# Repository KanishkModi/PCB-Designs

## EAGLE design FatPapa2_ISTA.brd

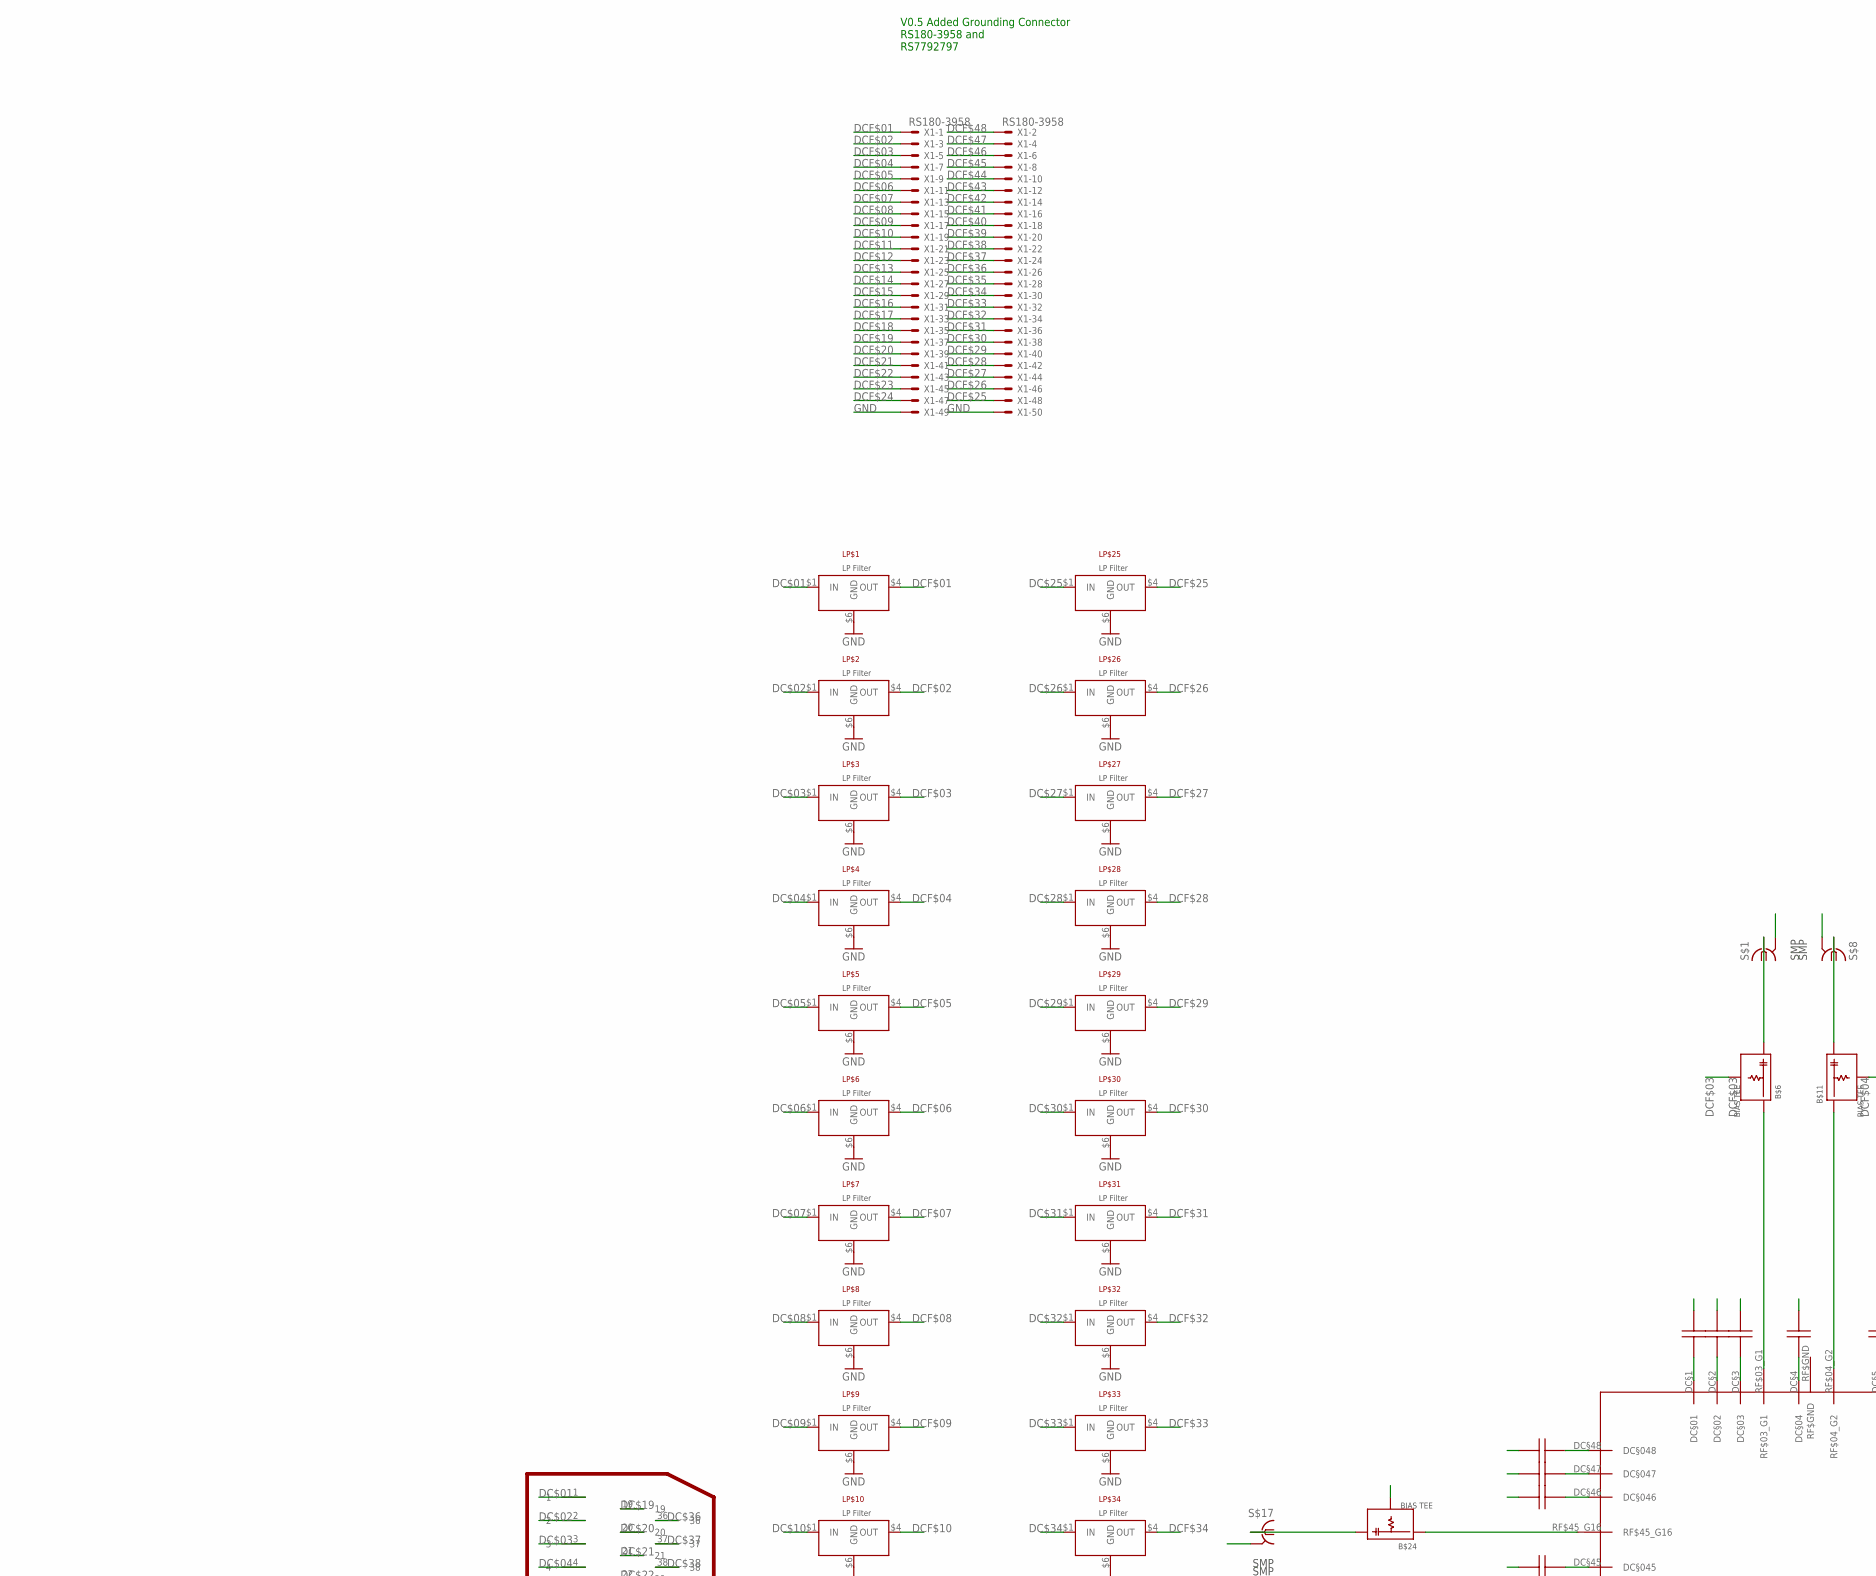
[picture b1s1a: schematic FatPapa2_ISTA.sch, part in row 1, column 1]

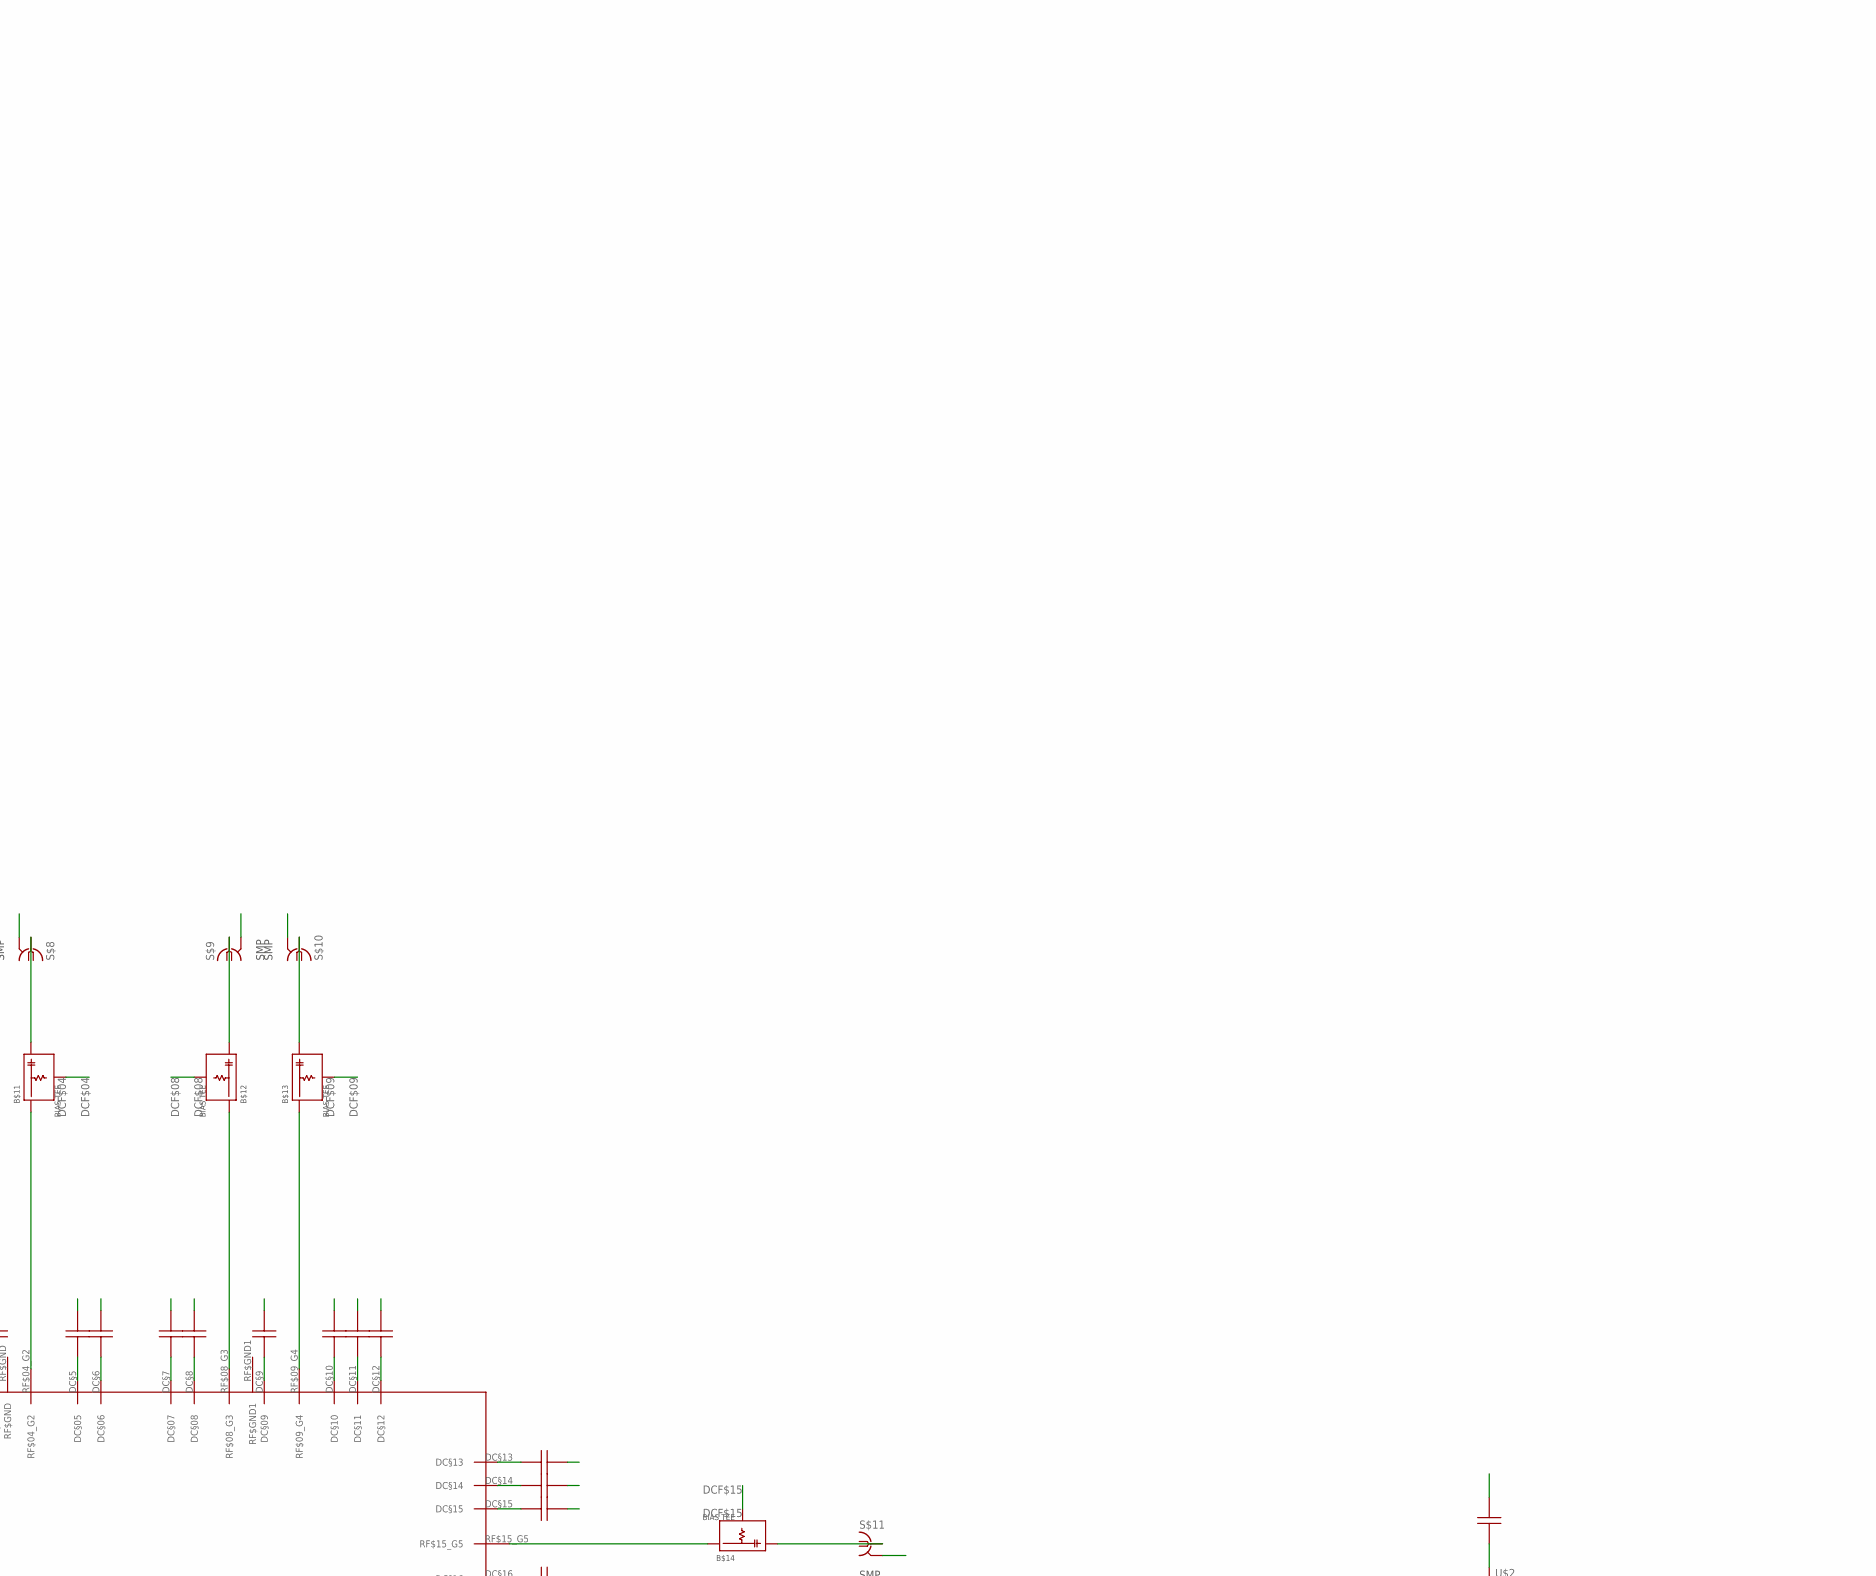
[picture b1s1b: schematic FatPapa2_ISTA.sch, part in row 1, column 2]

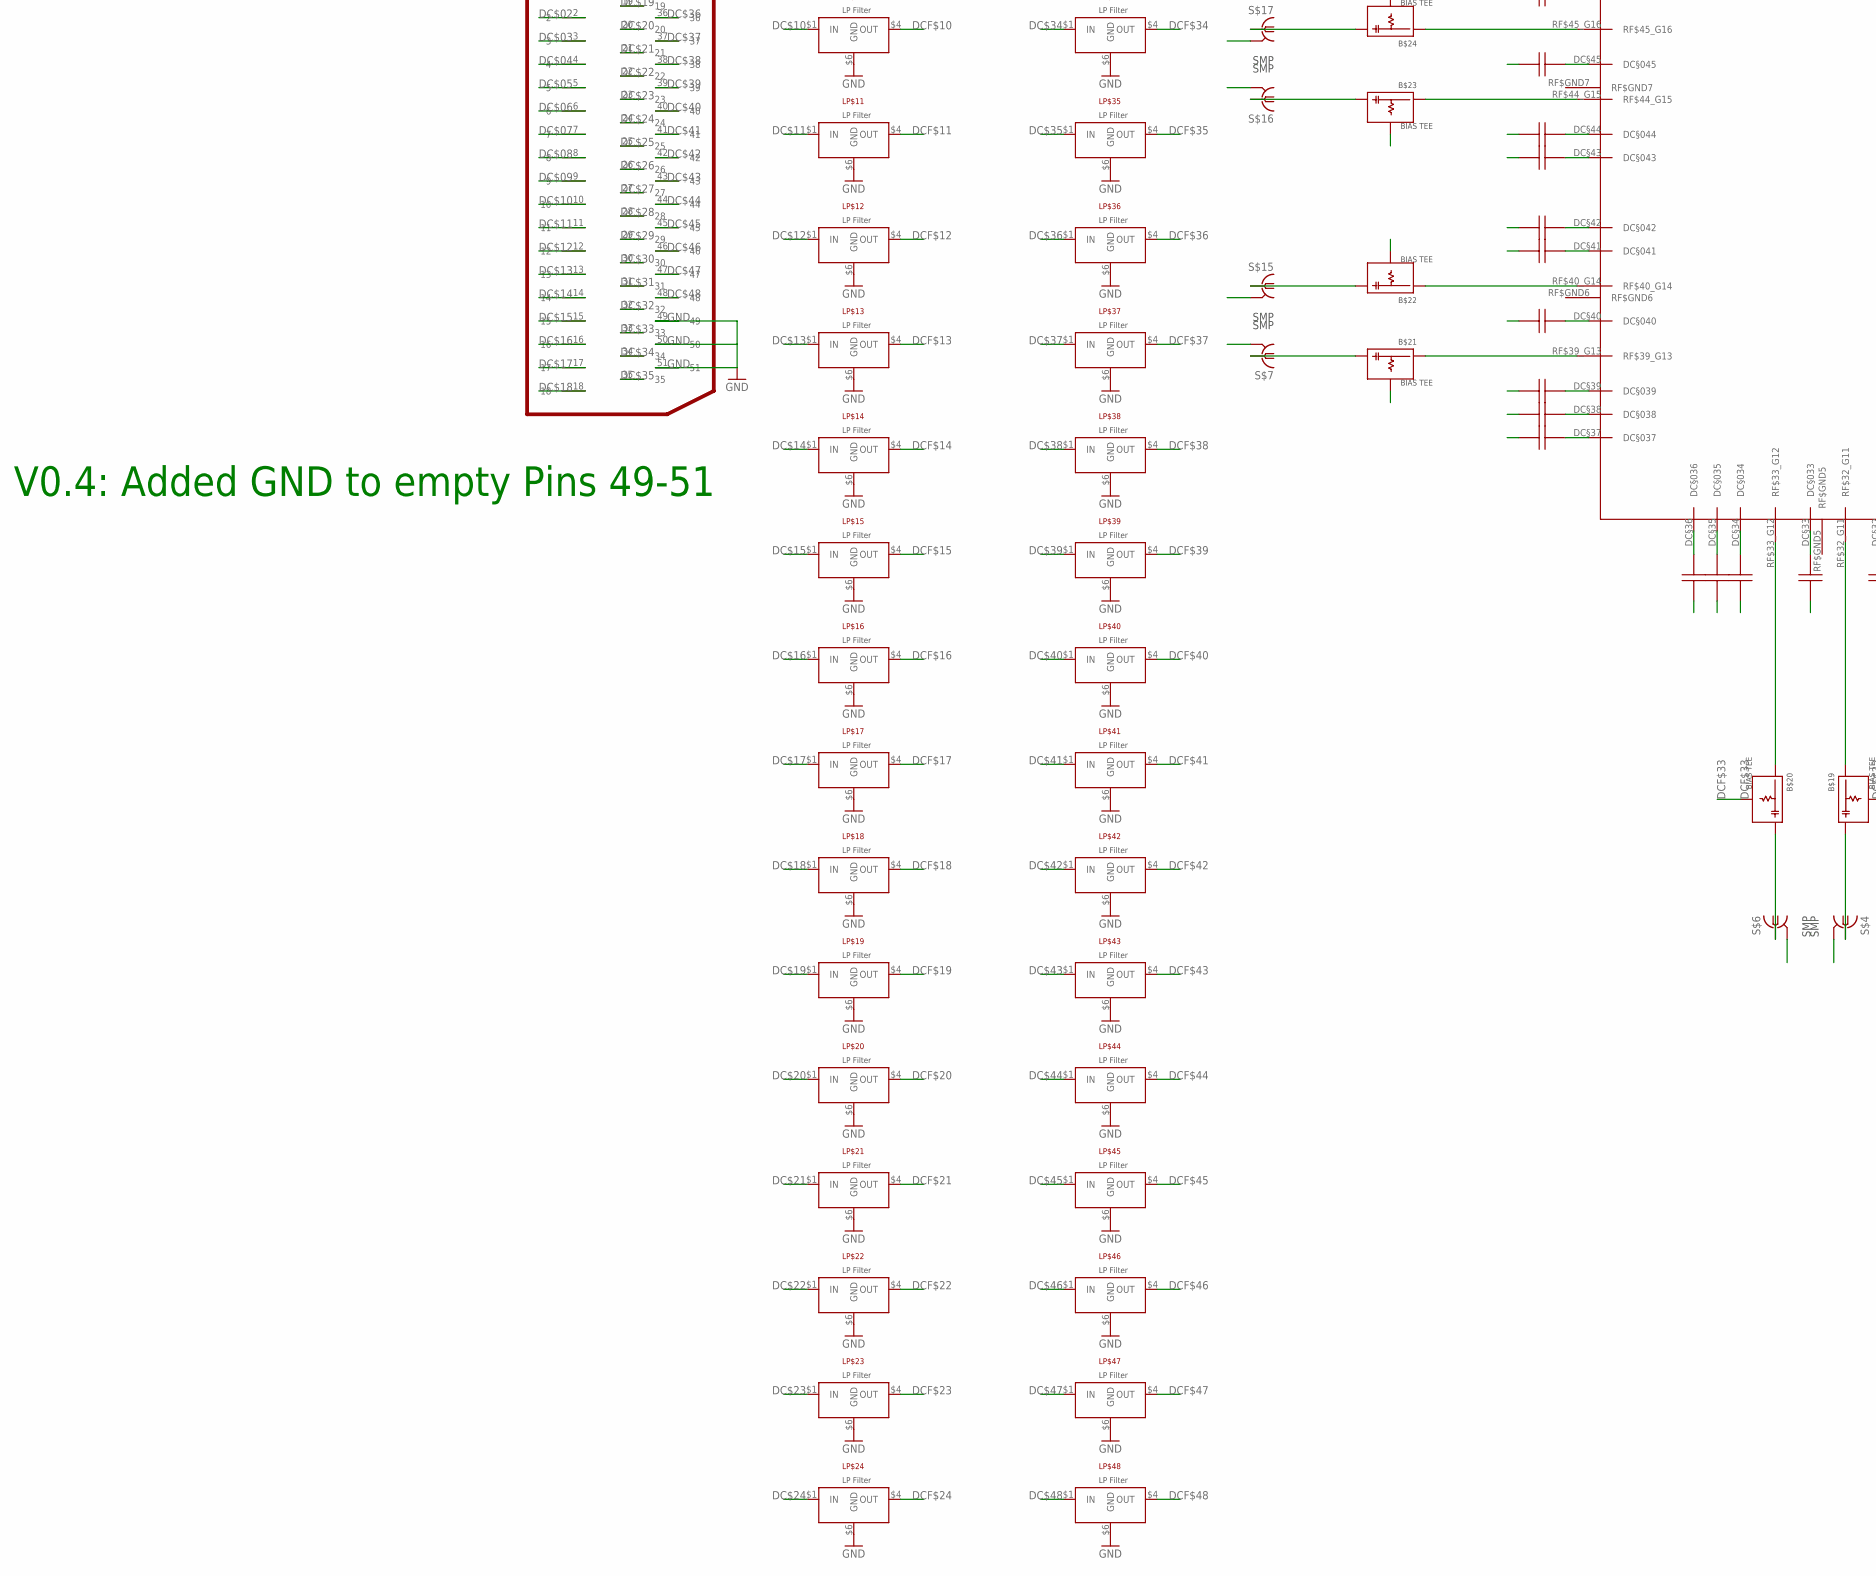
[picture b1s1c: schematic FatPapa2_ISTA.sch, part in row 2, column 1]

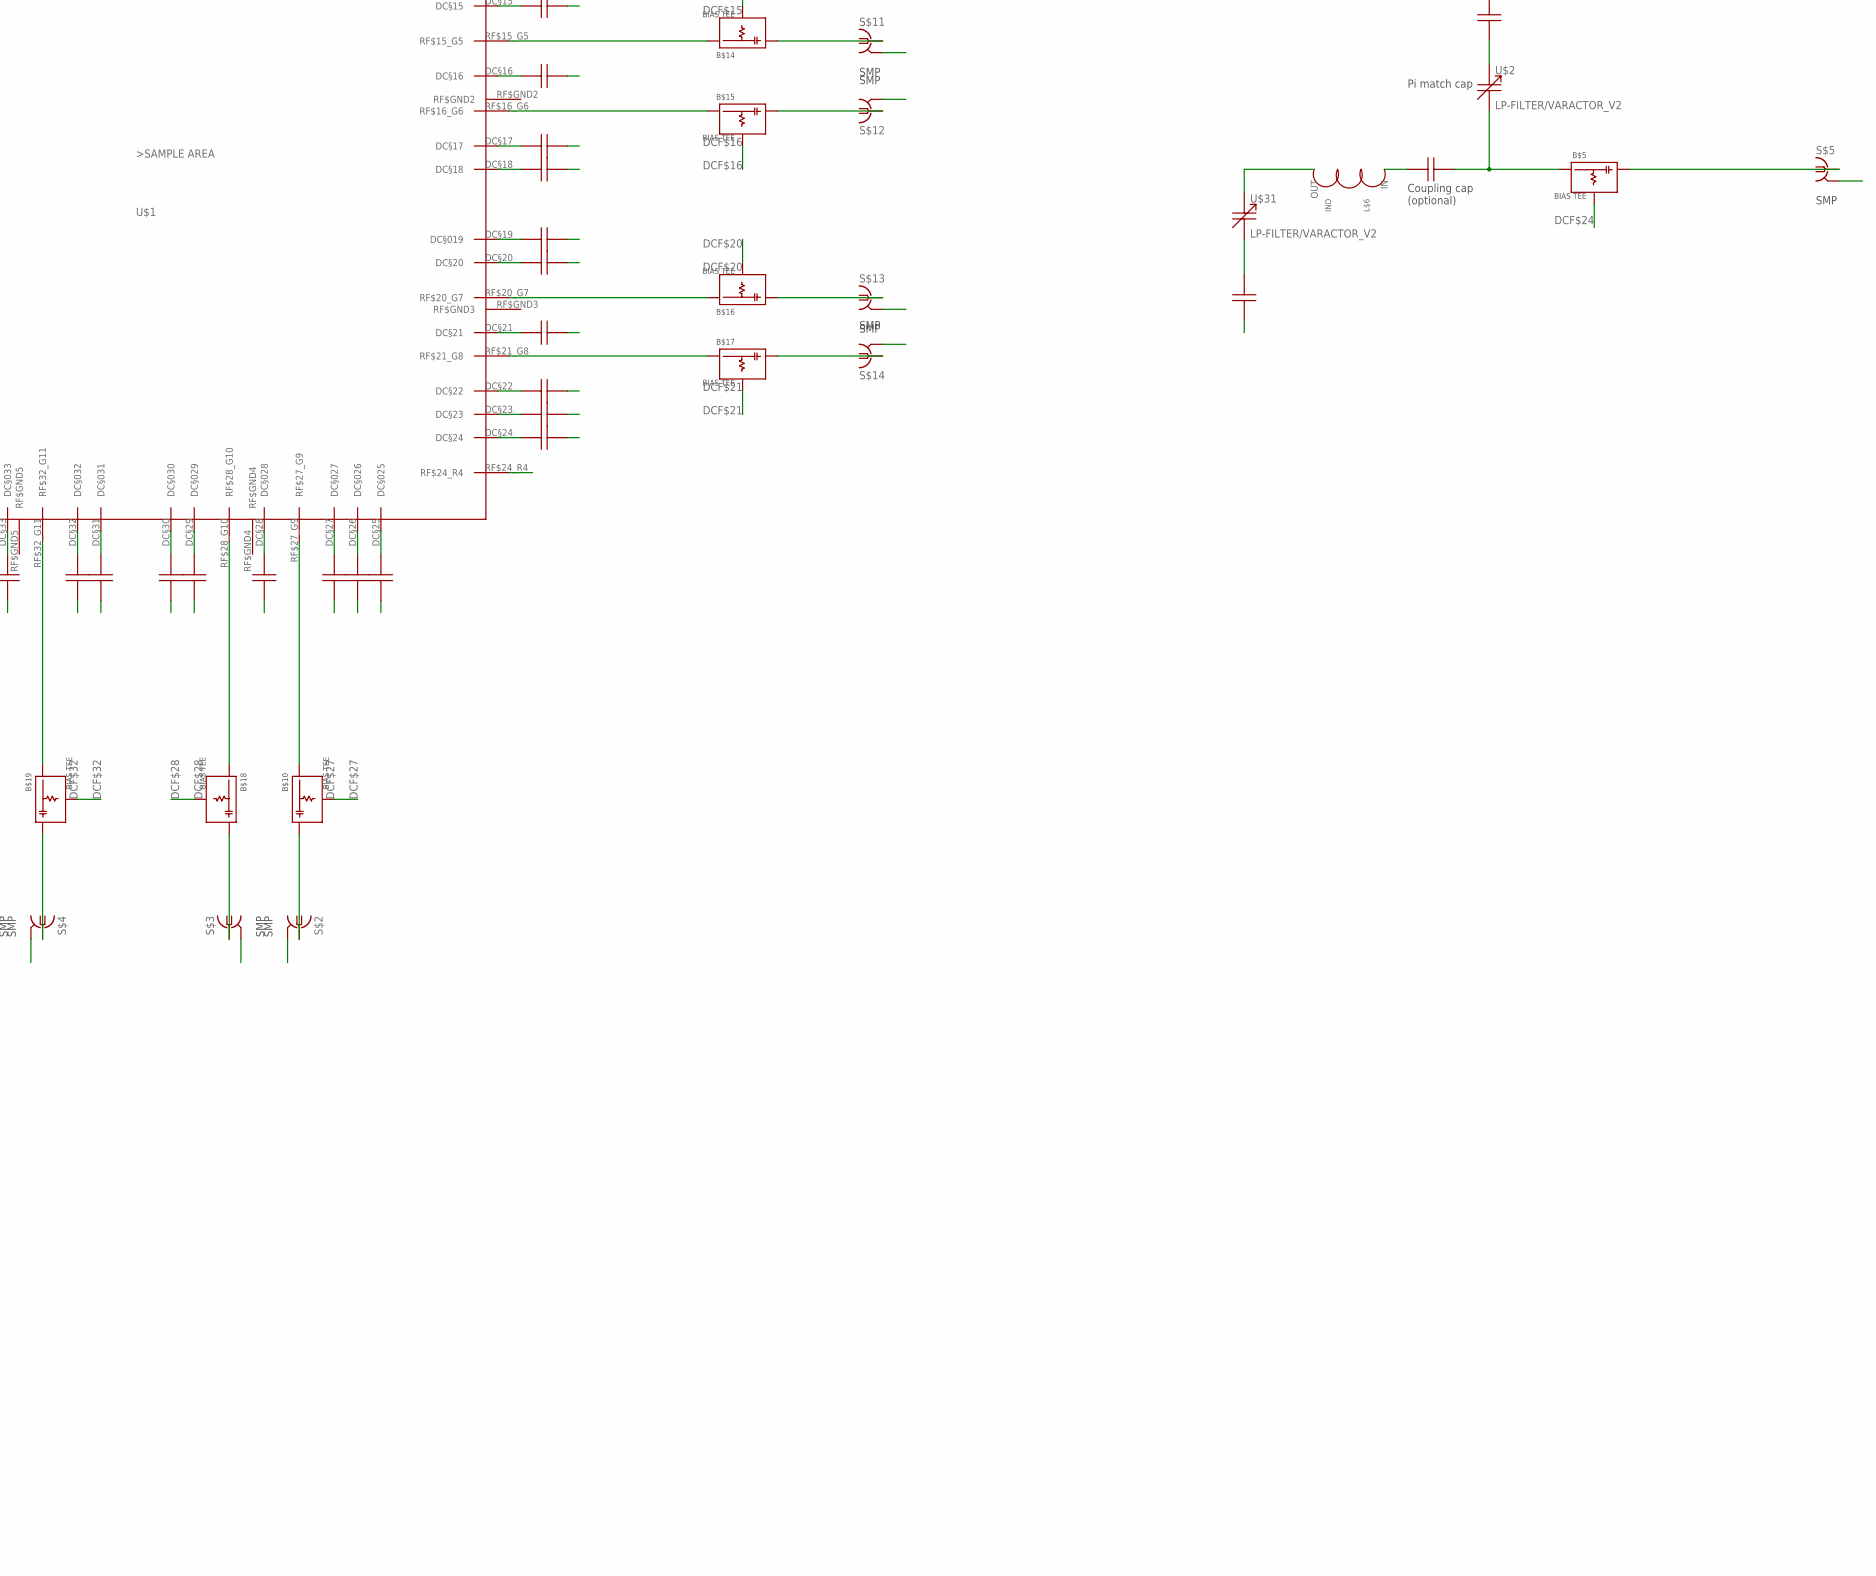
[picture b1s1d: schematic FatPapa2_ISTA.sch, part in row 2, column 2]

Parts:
B$5: BIASTEETHINUP; BIAS_TEE_UP_0603_THIN
B$6, B$10, B$11, B$14, B$15, B$18, B$21, B$22: BIASTEEDOWN1; BIAS_TEE_DOWN_0603
B$12, B$13, B$16, B$17, B$19, B$20, B$23, B$24: BIASTEEUP1; BIAS_TEE_UP_0603
L$6: L_MATCH
LP$1, LP$2, LP$3, LP$4, LP$5, LP$6, LP$7, LP$8, LP$9, LP$10, LP$11, LP$12, LP$13, LP$14, LP$15, LP$16, LP$17, LP$18, LP$19, LP$20, LP$21, LP$22, LP$23, LP$24, LP$25, LP$26, LP$27, LP$28, LP$29, LP$30, LP$31, LP$32, LP$33, LP$34, LP$35, LP$36, LP$37, LP$38, LP$39, LP$40, LP$41, LP$42, LP$43, LP$44, LP$45, LP$46, LP$47, LP$48: LP-FILTER/1-STAGETOP; LP-FILTER/1_STAGE/OS/0603_TOP
S$1, S$2, S$3, S$4, S$6, S$7, S$8, S$9, S$10, S$11, S$12, S$13, S$14, S$15, S$16, S$17: MC-921WIDE; SMP_STRAIGHT_MINI_WIDE
S$5: MC-921; SMP_STRAIGHT_MINI_WIDE_V1_01_ROUND
U$1: 48DC+24RF_V4.0
U$2, U$31: LP-FILTER/VARACTOR_V2
U$3, U$32: LP-FILTER/CAPACITOR/0603NORMAL; LP-FILTER/CAPACITOR/0603_BOTTOM_V2
U$25: 51_PIN_M83513/11-G
U$33, U$42, U$43, U$44, U$45, U$46, U$47, U$48, U$49, U$50, U$51, U$52, U$53, U$54, U$55, U$56, U$57, U$58, U$59, U$60, U$61, U$62, U$63, U$64, U$65, U$66, U$67, U$68, U$69, U$70, U$71, U$72, U$73, U$74, U$75, U$76, U$77, U$78, U$79, U$80, U$81, U$82, U$83, U$84, U$85, U$86, U$87, U$88, U$89: LP-FILTER/CAPACITOR/0603THIN; LP-FILTER/CAPACITOR/0603_BOTTOM
X1: RS180-3958; SMDSMALL87758-5016

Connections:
DC$01: LP$1.$1 (IN), U$25.1
DC$02: LP$2.$1 (IN), U$25.2
DC$03: LP$3.$1 (IN), U$25.3
DC$04: LP$4.$1 (IN), U$25.4
DC$05: LP$5.$1 (IN), U$25.5
DC$06: LP$6.$1 (IN), U$25.6
DC$07: LP$7.$1 (IN), U$25.7
DC$08: LP$8.$1 (IN), U$25.8
DC$09: LP$9.$1 (IN), U$25.9
DC$10: LP$10.$1 (IN), U$25.10
DC$11: LP$11.$1 (IN), U$25.11
DC$12: LP$12.$1 (IN), U$25.12
DC$13: LP$13.$1 (IN), U$25.13
DC$14: LP$14.$1 (IN), U$25.14
DC$15: LP$15.$1 (IN), U$25.15
DC$16: LP$16.$1 (IN), U$25.16
DC$17: LP$17.$1 (IN), U$25.17
DC$18: LP$18.$1 (IN), U$25.18
DC$19: LP$19.$1 (IN), U$25.19
DC$20: LP$20.$1 (IN), U$25.20
DC$21: LP$21.$1 (IN), U$25.21
DC$22: LP$22.$1 (IN), U$25.22
DC$23: LP$23.$1 (IN), U$25.23
DC$24: LP$24.$1 (IN), U$25.24
DC$25: LP$25.$1 (IN), U$25.25
DC$26: LP$26.$1 (IN), U$25.26
DC$27: LP$27.$1 (IN), U$25.27
DC$28: LP$28.$1 (IN), U$25.28
DC$29: LP$29.$1 (IN), U$25.29
DC$30: LP$30.$1 (IN), U$25.30
DC$31: LP$31.$1 (IN), U$25.31
DC$32: LP$32.$1 (IN), U$25.32
DC$33: LP$33.$1 (IN), U$25.33
DC$34: LP$34.$1 (IN), U$25.34
DC$35: LP$35.$1 (IN), U$25.35
DC$36: LP$36.$1 (IN), U$25.36
DC$37: LP$37.$1 (IN), U$25.37
DC$38: LP$38.$1 (IN), U$25.38
DC$39: LP$39.$1 (IN), U$25.39
DC$40: LP$40.$1 (IN), U$25.40
DC$41: LP$41.$1 (IN), U$25.41
DC$42: LP$42.$1 (IN), U$25.42
DC$43: LP$43.$1 (IN), U$25.43
DC$44: LP$44.$1 (IN), U$25.44
DC$45: LP$45.$1 (IN), U$25.45
DC$46: LP$46.$1 (IN), U$25.46
DC$47: LP$47.$1 (IN), U$25.47
DC$48: LP$48.$1 (IN), U$25.48
DCF$01: LP$1.$4 (OUT), U$1.DC§1 (DC§01), U$42.OUT (2), X1.P$1
DCF$02: LP$2.$4 (OUT), U$1.DC§2 (DC§02), U$43.OUT (2), X1.P$3
DCF$03: B$6.LF, LP$3.$4 (OUT), U$1.DC§3 (DC§03), U$44.OUT (2), X1.P$5
DCF$04: B$11.LF, LP$4.$4 (OUT), U$1.DC§4 (DC§04), U$45.OUT (2), X1.P$7
DCF$05: LP$5.$4 (OUT), U$1.DC§5 (DC§05), U$46.OUT (2), X1.P$9
DCF$06: LP$6.$4 (OUT), U$1.DC§6 (DC§06), U$47.OUT (2), X1.P$11
DCF$07: LP$7.$4 (OUT), U$1.DC§7 (DC§07), U$48.OUT (2), X1.P$13
DCF$08: B$12.LF, LP$8.$4 (OUT), U$1.DC§8 (DC§08), U$49.OUT (2), X1.P$15
DCF$09: B$13.LF, LP$9.$4 (OUT), U$1.DC§9 (DC§09), U$50.OUT (2), X1.P$17
DCF$10: LP$10.$4 (OUT), U$1.DC§10, U$51.OUT (2), X1.P$19
DCF$11: LP$11.$4 (OUT), U$1.DC§11, U$52.OUT (2), X1.P$21
DCF$12: LP$12.$4 (OUT), U$1.DC§12, U$53.OUT (2), X1.P$23
DCF$13: LP$13.$4 (OUT), U$1.DC§13, U$54.IN (1), X1.P$25
DCF$14: LP$14.$4 (OUT), U$1.DC§14, U$55.IN (1), X1.P$27
DCF$15: B$14.LF, LP$15.$4 (OUT), U$1.DC§15, U$56.IN (1), X1.P$29
DCF$16: B$15.LF, LP$16.$4 (OUT), U$1.DC§16, U$57.IN (1), X1.P$31
DCF$17: LP$17.$4 (OUT), U$1.DC§17, U$58.IN (1), X1.P$33
DCF$18: LP$18.$4 (OUT), U$1.DC§18, U$59.IN (1), X1.P$35
DCF$19: LP$19.$4 (OUT), U$1.DC§19 (DC§019), U$60.IN (1), X1.P$37
DCF$20: B$16.LF, LP$20.$4 (OUT), U$1.DC§20, U$61.IN (1), X1.P$39
DCF$21: B$17.LF, LP$21.$4 (OUT), U$1.DC§21, U$62.IN (1), X1.P$41
DCF$22: LP$22.$4 (OUT), U$1.DC§22, U$63.IN (1), X1.P$43
DCF$23: LP$23.$4 (OUT), U$1.DC§23, U$64.IN (1), X1.P$45
DCF$24: B$5.LF, LP$24.$4 (OUT), U$1.DC§24, U$65.IN (1), X1.P$47
DCF$25: LP$25.$4 (OUT), U$1.DC§25 (DC§025), U$31.OUT1 (2), U$32.OUT (2), U$66.IN (1), X1.P$48
DCF$26: LP$26.$4 (OUT), U$1.DC§26 (DC§026), U$2.OUT (1), U$3.IN (1), U$67.IN (1), X1.P$46
DCF$27: B$10.LF, LP$27.$4 (OUT), U$1.DC§27 (DC§027), U$68.IN (1), X1.P$44
DCF$28: B$18.LF, LP$28.$4 (OUT), U$1.DC§28 (DC§028), U$69.IN (1), X1.P$42
DCF$29: LP$29.$4 (OUT), U$1.DC§29 (DC§029), U$70.IN (1), X1.P$40
DCF$30: LP$30.$4 (OUT), U$1.DC§30 (DC§030), U$71.IN (1), X1.P$38
DCF$31: LP$31.$4 (OUT), U$1.DC§31 (DC§031), U$72.IN (1), X1.P$36
DCF$32: B$19.LF, LP$32.$4 (OUT), U$1.DC§32 (DC§032), U$73.IN (1), X1.P$34
DCF$33: B$20.LF, LP$33.$4 (OUT), U$1.DC§33 (DC§033), U$74.IN (1), X1.P$32
DCF$34: LP$34.$4 (OUT), U$1.DC§34 (DC§034), U$75.IN (1), X1.P$30
DCF$35: LP$35.$4 (OUT), U$1.DC§35 (DC§035), U$76.IN (1), X1.P$28
DCF$36: LP$36.$4 (OUT), U$1.DC§36 (DC§036), U$77.IN (1), X1.P$26
DCF$37: LP$37.$4 (OUT), U$1.DC§37 (DC§037), U$78.IN (1), X1.P$24
DCF$38: LP$38.$4 (OUT), U$1.DC§38 (DC§038), U$79.IN (1), X1.P$22
DCF$39: B$21.LF, LP$39.$4 (OUT), U$1.DC§39 (DC§039), U$80.IN (1), X1.P$20
DCF$40: B$22.LF, LP$40.$4 (OUT), U$1.DC§40 (DC§040), U$81.IN (1), X1.P$18
DCF$41: LP$41.$4 (OUT), U$1.DC§41 (DC§041), U$82.IN (1), X1.P$16
DCF$42: LP$42.$4 (OUT), U$1.DC§42 (DC§042), U$83.IN (1), X1.P$14
DCF$43: LP$43.$4 (OUT), U$1.DC§43 (DC§043), U$84.IN (1), X1.P$12
DCF$44: B$23.LF, LP$44.$4 (OUT), U$1.DC§44 (DC§044), U$85.IN (1), X1.P$10
DCF$45: B$24.LF, LP$45.$4 (OUT), U$1.DC§45 (DC§045), U$86.IN (1), X1.P$8
DCF$46: LP$46.$4 (OUT), U$1.DC§46 (DC§046), U$87.IN (1), X1.P$6
DCF$47: LP$47.$4 (OUT), U$1.DC§47 (DC§047), U$88.IN (1), X1.P$4
DCF$48: LP$48.$4 (OUT), U$1.DC§48 (DC§048), U$89.IN (1), X1.P$2
GND: LP$1.$6 (GND), LP$2.$6 (GND), LP$3.$6 (GND), LP$4.$6 (GND), LP$5.$6 (GND), LP$6.$6 (GND), LP$7.$6 (GND), LP$8.$6 (GND), LP$9.$6 (GND), LP$10.$6 (GND), LP$11.$6 (GND), LP$12.$6 (GND), LP$13.$6 (GND), LP$14.$6 (GND), LP$15.$6 (GND), LP$16.$6 (GND), LP$17.$6 (GND), LP$18.$6 (GND), LP$19.$6 (GND), LP$20.$6 (GND), LP$21.$6 (GND), LP$22.$6 (GND), LP$23.$6 (GND), LP$24.$6 (GND), LP$25.$6 (GND), LP$26.$6 (GND), LP$27.$6 (GND), LP$28.$6 (GND), LP$29.$6 (GND), LP$30.$6 (GND), LP$31.$6 (GND), LP$32.$6 (GND), LP$33.$6 (GND), LP$34.$6 (GND), LP$35.$6 (GND), LP$36.$6 (GND), LP$37.$6 (GND), LP$38.$6 (GND), LP$39.$6 (GND), LP$40.$6 (GND), LP$41.$6 (GND), LP$42.$6 (GND), LP$43.$6 (GND), LP$44.$6 (GND), LP$45.$6 (GND), LP$46.$6 (GND), LP$47.$6 (GND), LP$48.$6 (GND), S$1.2@1 (GND), S$1.2@2 (GND), S$2.2@1 (GND), S$2.2@2 (GND), S$3.2@1 (GND), S$3.2@2 (GND), S$4.2@1 (GND), S$4.2@2 (GND), S$5.GND, S$5.GND@1 (GND), S$6.2@1 (GND), S$6.2@2 (GND), S$7.2@1 (GND), S$7.2@2 (GND), S$8.2@1 (GND), S$8.2@2 (GND), S$9.2@1 (GND), S$9.2@2 (GND), S$10.2@1 (GND), S$10.2@2 (GND), S$11.2@1 (GND), S$11.2@2 (GND), S$12.2@1 (GND), S$12.2@2 (GND), S$13.2@1 (GND), S$13.2@2 (GND), S$14.2@1 (GND), S$14.2@2 (GND), S$15.2@1 (GND), S$15.2@2 (GND), S$16.2@1 (GND), S$16.2@2 (GND), S$17.2@1 (GND), S$17.2@2 (GND), U$3.OUT (2), U$25.49, U$25.50, U$25.51, U$32.IN (1), U$42.IN (1), U$43.IN (1), U$44.IN (1), U$45.IN (1), U$46.IN (1), U$47.IN (1), U$48.IN (1), U$49.IN (1), U$50.IN (1), U$51.IN (1), U$52.IN (1), U$53.IN (1), U$54.OUT (2), U$55.OUT (2), U$56.OUT (2), U$57.OUT (2), U$58.OUT (2), U$59.OUT (2), U$60.OUT (2), U$61.OUT (2), U$62.OUT (2), U$63.OUT (2), U$64.OUT (2), U$65.OUT (2), U$66.OUT (2), U$67.OUT (2), U$68.OUT (2), U$69.OUT (2), U$70.OUT (2), U$71.OUT (2), U$72.OUT (2), U$73.OUT (2), U$74.OUT (2), U$75.OUT (2), U$76.OUT (2), U$77.OUT (2), U$78.OUT (2), U$79.OUT (2), U$80.OUT (2), U$81.OUT (2), U$82.OUT (2), U$83.OUT (2), U$84.OUT (2), U$85.OUT (2), U$86.OUT (2), U$87.OUT (2), U$88.OUT (2), U$89.OUT (2), X1.P$49, X1.P$50
unnamed: B$6.HF, S$1.1
unnamed: B$11.HF, S$8.1
unnamed: B$12.HF, S$9.1
unnamed: B$14.OUT, U$1.RF$15_G5
unnamed: B$15.OUT, U$1.RF$16_G6
unnamed: B$13.HF, S$10.1
unnamed: B$14.HF, S$11.1
unnamed: B$16.OUT, U$1.RF$20_G7
unnamed: B$17.OUT, U$1.RF$21_G8
unnamed: B$5.HF, S$5.1
unnamed: B$15.HF, S$12.1
unnamed: B$16.HF, S$13.1
unnamed: B$17.HF, S$14.1
unnamed: B$6.OUT, U$1.RF$03_G1
unnamed: B$11.OUT, U$1.RF$04_G2
unnamed: B$12.OUT, U$1.RF$08_G3
unnamed: B$13.OUT, U$1.RF$09_G4
unnamed: L$6.IN, U$33.IN (1)
unnamed: B$10.HF, S$2.1
unnamed: B$18.HF, S$3.1
unnamed: B$18.OUT, U$1.RF$28_G10
unnamed: B$10.OUT, U$1.RF$27_G9
unnamed: B$19.HF, S$4.1
unnamed: B$20.HF, S$6.1
unnamed: B$20.OUT, U$1.RF$33_G12
unnamed: B$19.OUT, U$1.RF$32_G11
unnamed: B$21.HF, S$7.1
unnamed: B$22.HF, S$15.1
unnamed: B$23.HF, S$16.1
unnamed: B$24.HF, S$17.1
unnamed: B$24.OUT, U$1.RF$45_G16
unnamed: B$23.OUT, U$1.RF$44_G15
unnamed: B$22.OUT, U$1.RF$40_G14
unnamed: B$21.OUT, U$1.RF$39_G13
RF$6: B$5.OUT, U$2.OUT1 (2), U$33.OUT (2)
RF$R4: L$6.OUT, U$1.RF$24_R4, U$31.OUT (1)

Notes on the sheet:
Pi match cap
Coupling cap (optional)
V0.4: Added GND to empty Pins 49-51
V0.5 Added Grounding Connector RS180-3958 and RS7792797

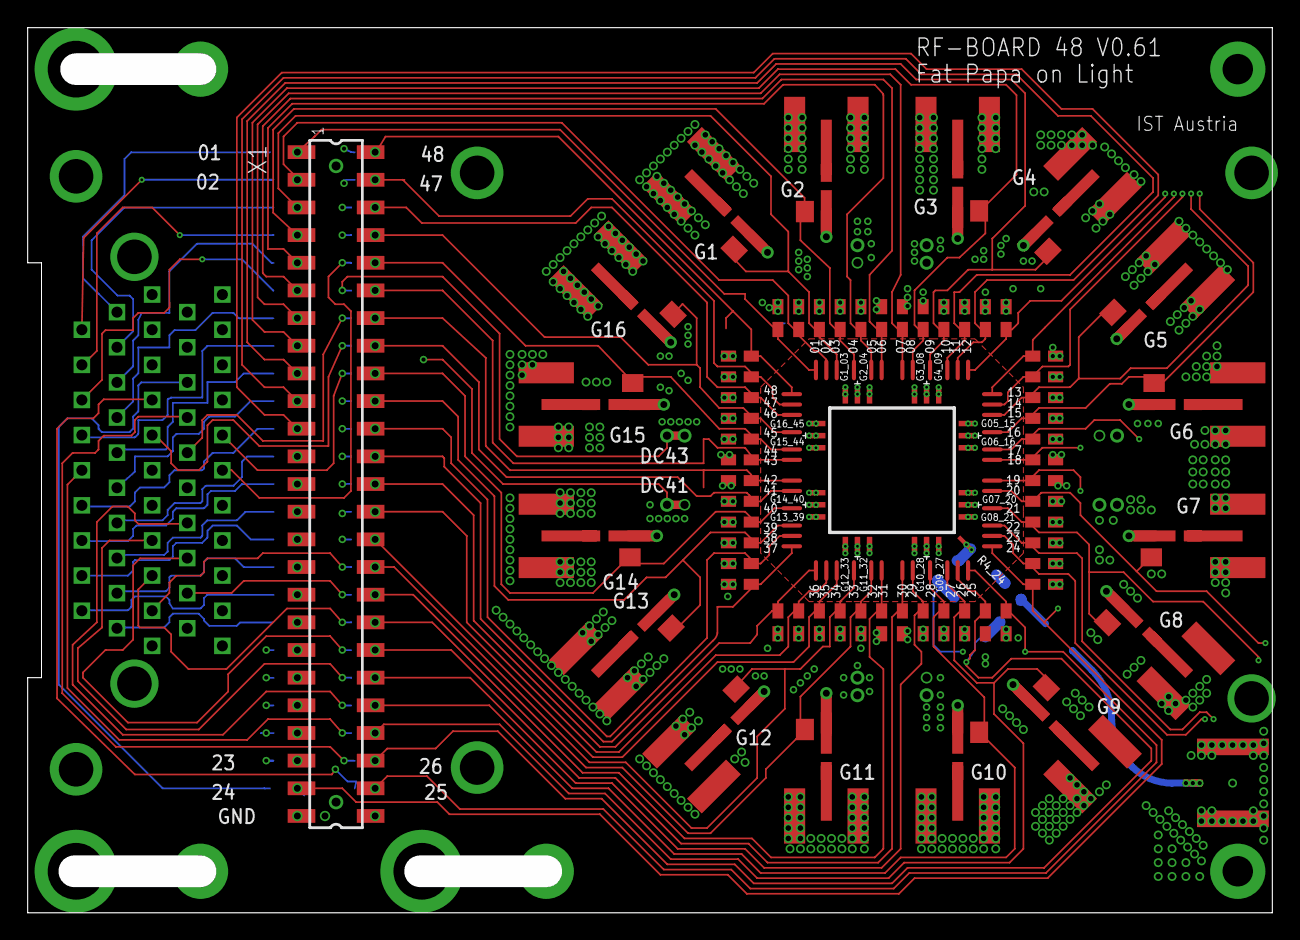
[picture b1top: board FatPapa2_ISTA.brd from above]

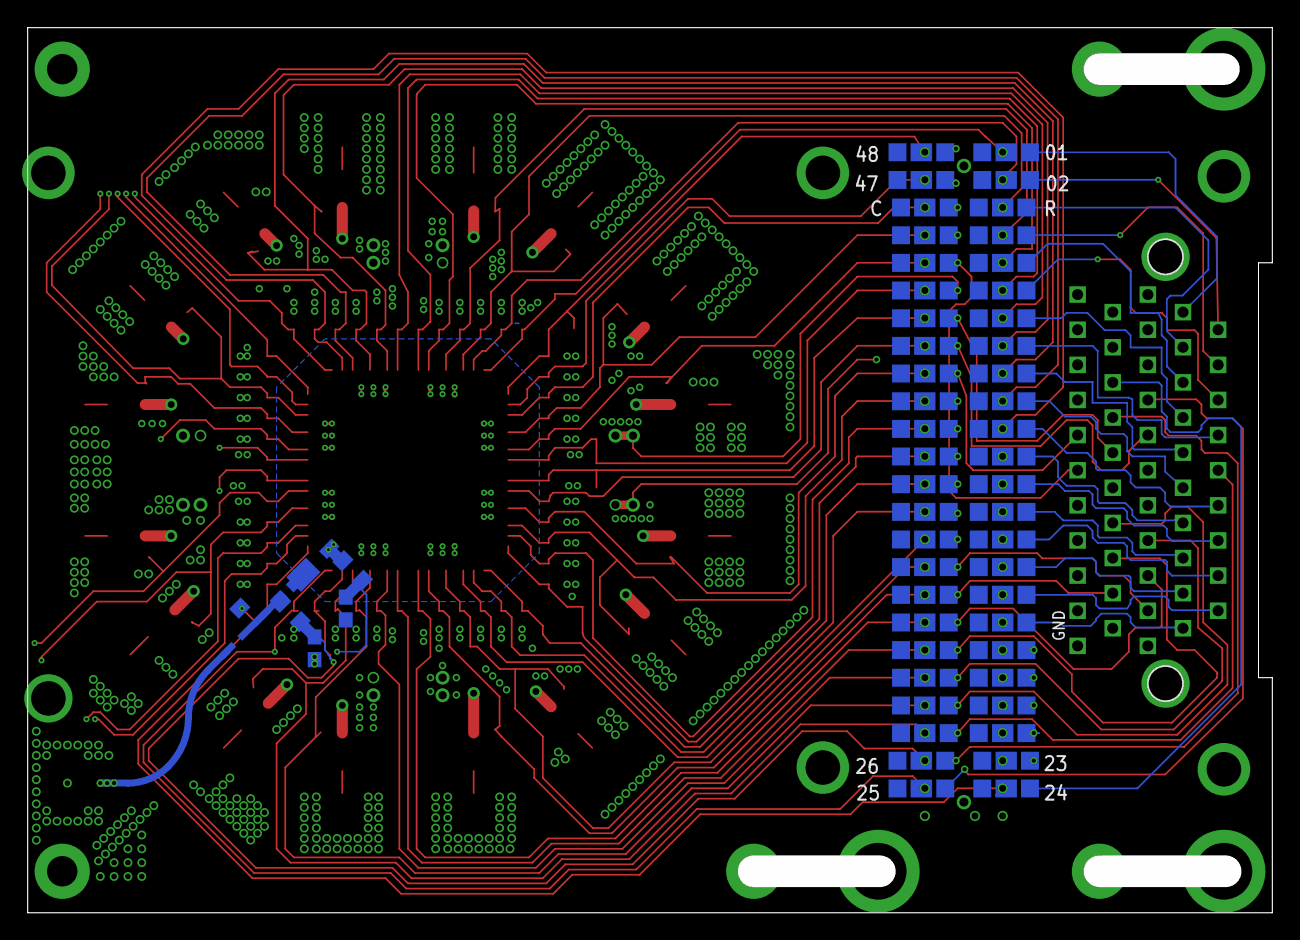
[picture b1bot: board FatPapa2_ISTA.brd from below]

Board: 6 copper layers, 90.0 x 64.0 mm, 139 parts (99 on the bottom side), 133 nets.
